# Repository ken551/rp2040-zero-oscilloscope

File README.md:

# rp2040-zero-oscilloscope
[picoLabo](https://picolabo.org/)様によるRaspberry Pi Pico オシロスコープと同等のものを、Waveshare社の[RP2040-Zero](https://www.waveshare.com/wiki/RP2040-Zero)を使って実現する、RP2040-Zero-オシロスコープ の回路図です。

> [!CAUTION]
> 本バージョン基板（v1）は回路の**配線ミス**があり、**パターンカット・空中配線**が必須です。
>

フリスクのケースに（~~無理やり~~）入るサイズです。

## **注意**
本バージョンの回路には**間違いがあります。**

## 回路図
[picoLabo](https://picolabo.org/)様の[Raspberry Pi Pico用オシロスコープ基板DIYキット PL2302KIT](https://picolabo.org/pl2302kit/)をベースにしています。小サイズ化のため、ベースの回路図から以下のように変更しています。

* アナログ入力をAC/DC両対応からDCのみに限定
* デジタル入力を8ch→4chに削減
* 信号出力端子を削除

### 使用ライブラリ
* [RP2040-Zero-KiCAD](https://github.com/dj505/RP2040-Zero-KiCAD) (by @dj505)

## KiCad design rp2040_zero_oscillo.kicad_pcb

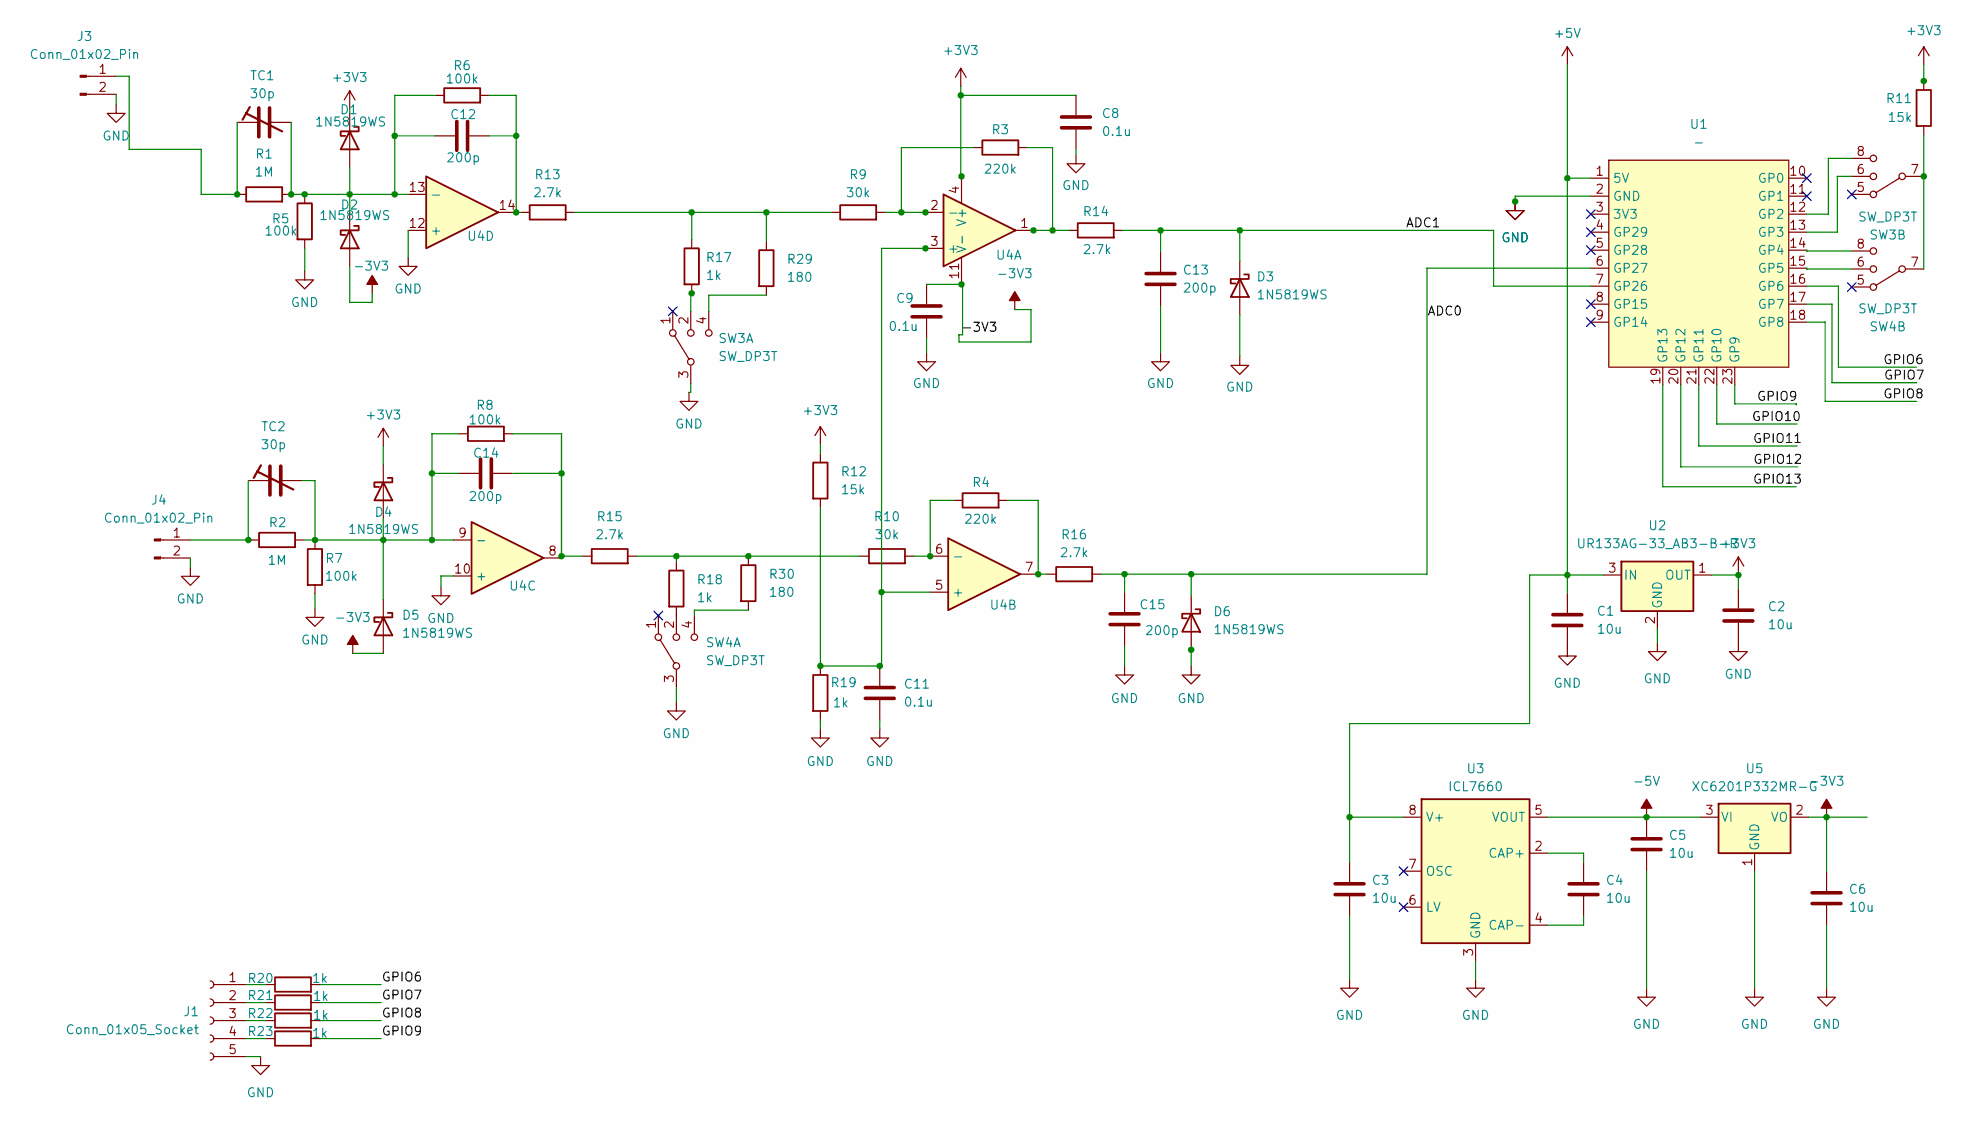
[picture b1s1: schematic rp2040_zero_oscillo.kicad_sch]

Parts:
C1, C2, C3, C4, C5, C6: 10u; C_0805_2012Metric_Pad1.18x1.45mm_HandSolder
C8, C9, C11: 0.1u; C_0603_1608Metric_Pad1.08x0.95mm_HandSolder
C12, C13, C14, C15: 200p; C_0603_1608Metric_Pad1.08x0.95mm_HandSolder
D1, D2, D3, D4, D5, D6: 1N5819WS; D_SOD-323_HandSoldering
J1: Conn_01x05_Socket; PinSocket_1x05_P2.54mm_Horizontal
J3, J4: Conn_01x02_Pin; PinSocket_1x02_P2.54mm_Vertical
R1, R2: 1M; R_0603_1608Metric_Pad0.98x0.95mm_HandSolder
R3, R4: 220k; R_0603_1608Metric_Pad0.98x0.95mm_HandSolder
R5, R6, R7, R8: 100k; R_0603_1608Metric_Pad0.98x0.95mm_HandSolder
R9, R10: 30k; R_0603_1608Metric_Pad0.98x0.95mm_HandSolder
R11, R12: 15k; R_0603_1608Metric_Pad0.98x0.95mm_HandSolder
R13, R14, R15, R16: 2.7k; R_0603_1608Metric_Pad0.98x0.95mm_HandSolder
R17, R18, R19, R20, R21, R22, R23: 1k; R_0603_1608Metric_Pad0.98x0.95mm_HandSolder
R29, R30: 180; R_0603_1608Metric_Pad0.98x0.95mm_HandSolder
SW3, SW4: SW_DP3T; DP3T_MSS23D18
TC1, TC2: 30p; TMCV01-10P100VB
U1: -; RP2040 Zero
U2: UR133AG-33_AB3-B-R; SOT-89-3_Handsoldering
U3: ICL7660; SOIC-8_3.9x4.9mm_P1.27mm
U4: SOIC-14_3.9x8.7mm_P1.27mm
U5: XC6201P332MR-G; SOT-23-3

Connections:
+3V3: C2.1, C8.1, D1.1 (K), D4.1 (K), R11.1, R12.1, U2.1 (OUT), U4.4 (V+)
+5V: C1.1, C3.1, U1.1 (5V), U2.3 (IN), U3.8 (V+)
-3V3: C6.1, C9.1, D2.2 (A), D5.2 (A), U4.11 (V-), U5.2 (VO)
-5V: C5.1, U3.5 (VOUT), U5.3 (VI)
/ADC0: C15.1, D6.1 (K), R16.2, U1.6 (GP27)
/ADC1: C13.1, D3.1 (K), R14.2, U1.7 (GP26)
/GPIO6: R20.2, U1.16 (GP6)
/GPIO7: R21.2, U1.17 (GP7)
/GPIO8: R22.2, U1.18 (GP8)
/GPIO9: R23.2, U1.23 (GP9)
/GPIO10: U1.22 (GP10)
/GPIO11: U1.21 (GP11)
/GPIO12: U1.20 (GP12)
/GPIO13: U1.19 (GP13)
GND: C1.2, C2.2, C3.2, C5.2, C6.2, C8.2, C9.2, C11.2, C13.2, C15.2, D3.2 (A), D6.2 (A), J1.5, J3.2, J4.2, R5.2, R7.2, R19.2, SW3.3, SW4.3, U1.2 (GND), U2.2 (GND), U3.3 (GND), U4.10 (+), U4.12 (+), U5.1 (GND)
unnamed: C12.2, R6.2, R13.1, U4.14
unnamed: C14.2, R8.2, R15.1, U4.8
unnamed: C12.1, D1.2 (A), D2.1 (K), R1.2, R5.1, R6.1, TC1.2, U4.13 (-)
unnamed: C14.1, D4.2 (A), D5.1 (K), R2.2, R7.1, R8.1, TC2.2, U4.9 (-)
unnamed: J1.1, R20.1
unnamed: J1.2, R21.1
unnamed: J1.3, R22.1
unnamed: J1.4, R23.1
unnamed: J3.1, R1.1, TC1.1
unnamed: J4.1, R2.1, TC2.1
unnamed: R10.1, R15.2, R18.1, R30.1
unnamed: R11.2, SW3.7, SW4.7
unnamed: R9.1, R13.2, R17.1, R29.1
unnamed: R3.2, R14.1, U4.1
unnamed: R4.2, R16.1, U4.7
unnamed: R17.2, SW3.2
unnamed: R18.2, SW4.2
unnamed: R29.2, SW3.4
unnamed: R30.2, SW4.4
unnamed: SW3.8, U1.12 (GP2)
unnamed: SW3.6, U1.13 (GP3)
unnamed: SW4.8, U1.14 (GP4)
unnamed: SW4.6, U1.15 (GP5)
unnamed: C4.1, U3.2 (CAP+)
unnamed: C4.2, U3.4 (CAP-)
unnamed: C11.1, R12.2, R19.1, U4.3 (+), U4.5 (+)
unnamed: R3.1, R9.2, U4.2 (-)
unnamed: R4.1, R10.2, U4.6 (-)

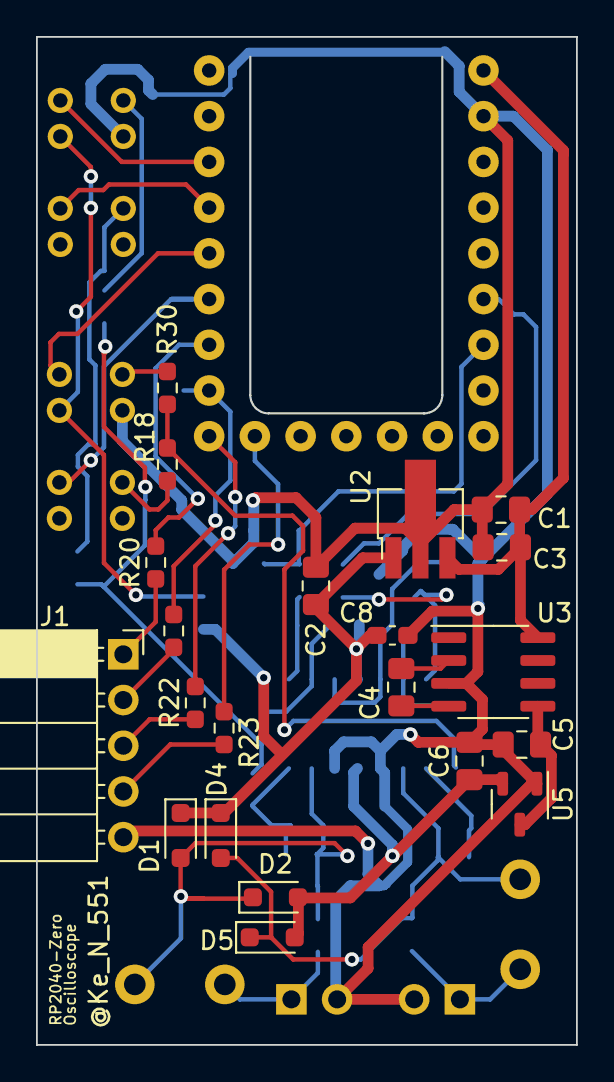
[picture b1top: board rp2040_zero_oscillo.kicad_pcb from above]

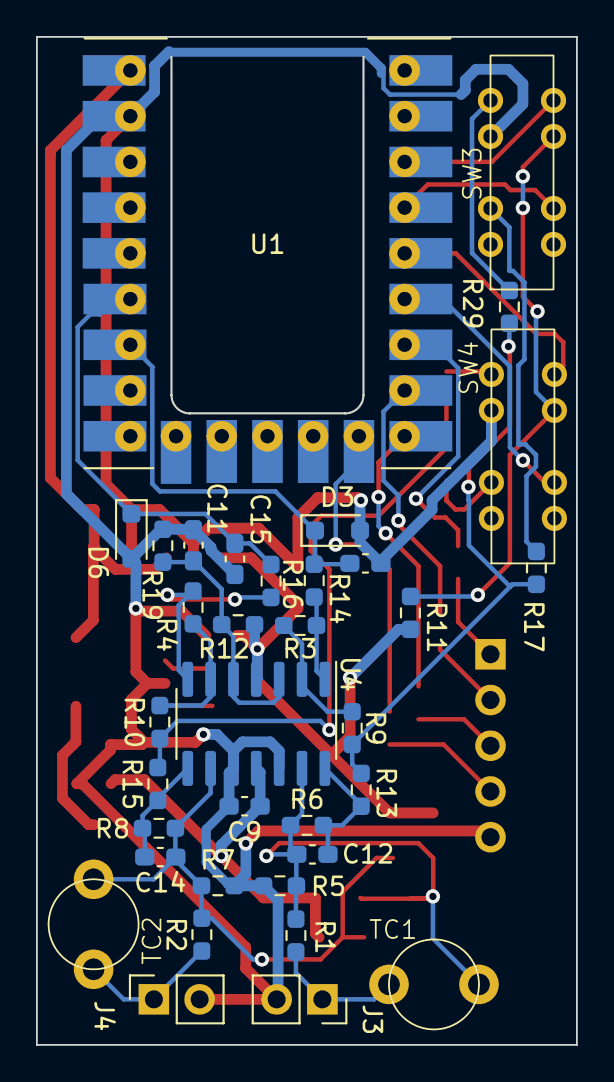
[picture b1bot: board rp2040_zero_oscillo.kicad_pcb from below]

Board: 2 copper layers, 30.0 x 56.0 mm, 56 parts (35 on the bottom side), 39 nets.

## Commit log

2023-11-19 my first commit
2023-11-20 概要を記載@
2023-12-09 配線ミスの注意事項を追記、ドキュメント画像をリサイズ
